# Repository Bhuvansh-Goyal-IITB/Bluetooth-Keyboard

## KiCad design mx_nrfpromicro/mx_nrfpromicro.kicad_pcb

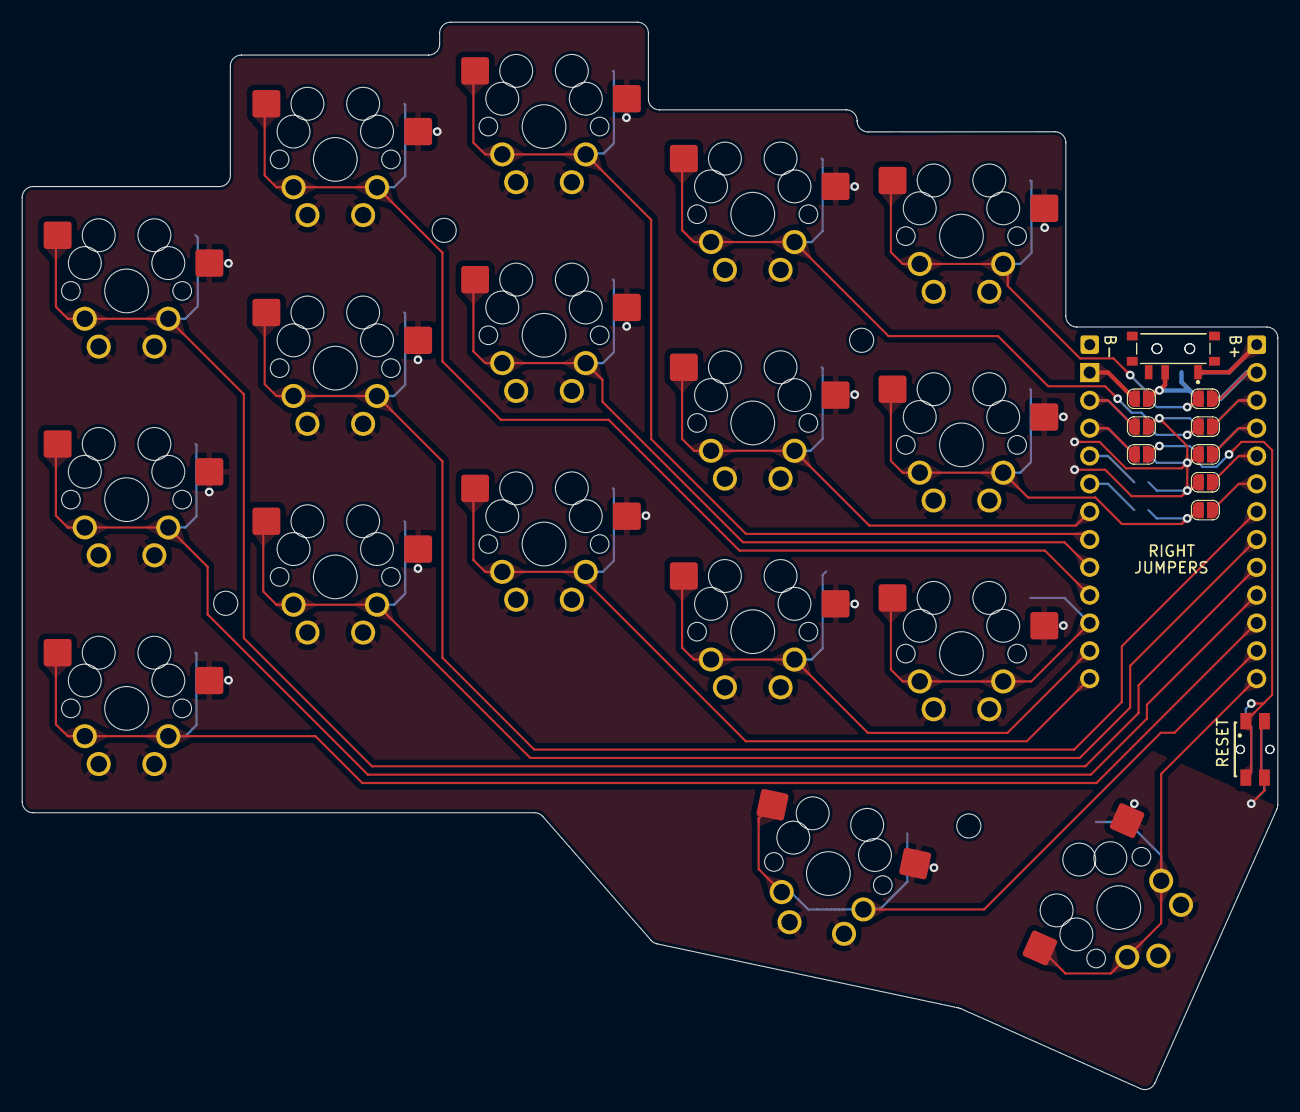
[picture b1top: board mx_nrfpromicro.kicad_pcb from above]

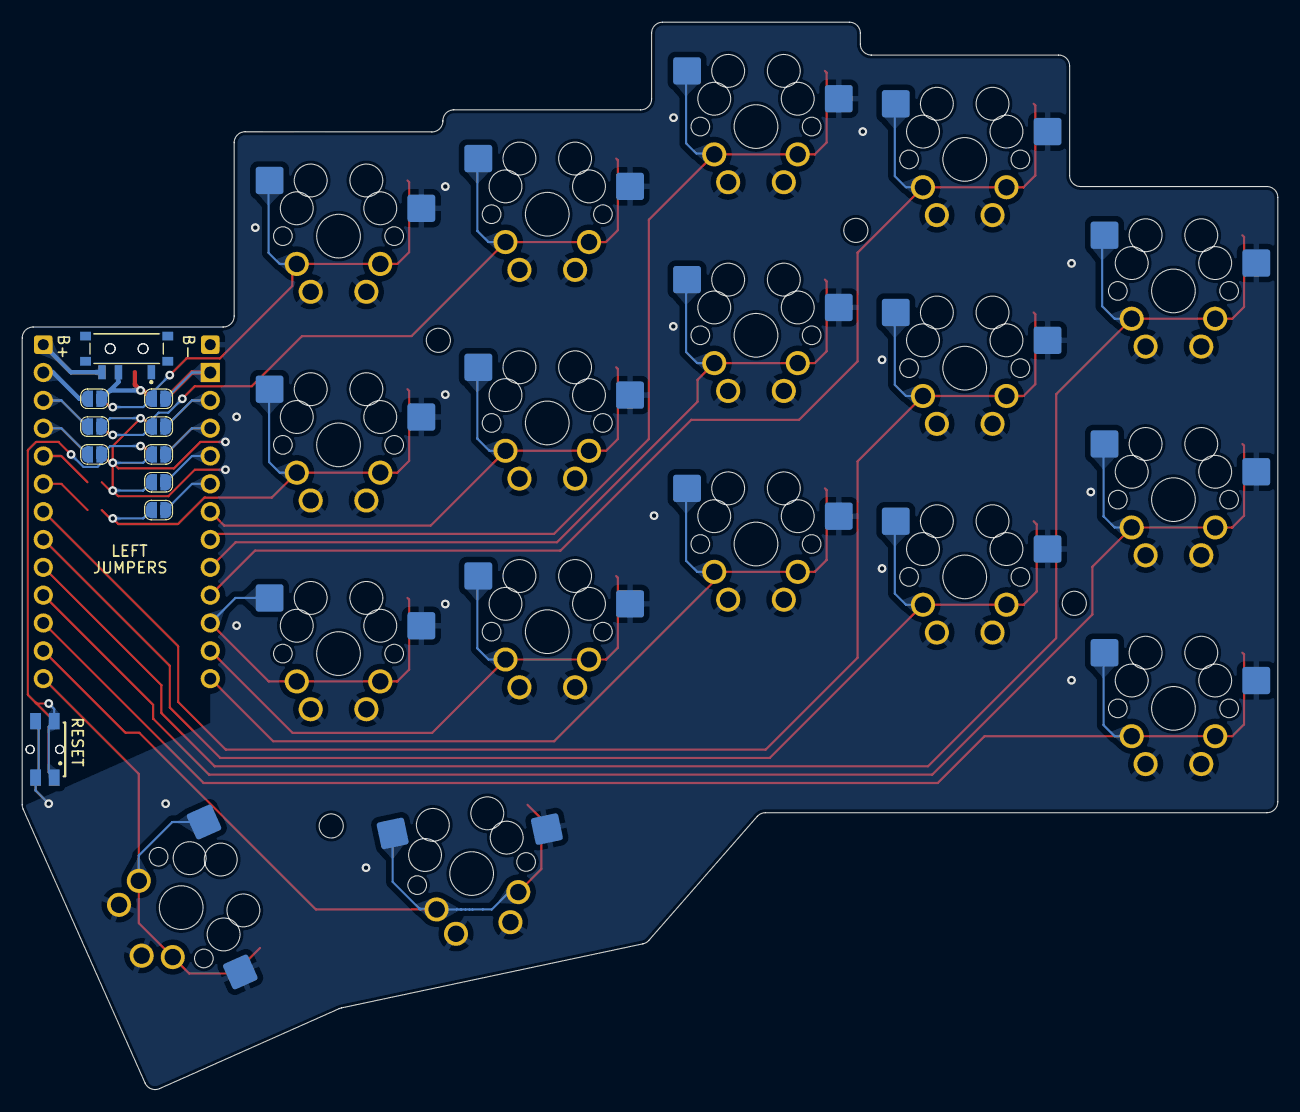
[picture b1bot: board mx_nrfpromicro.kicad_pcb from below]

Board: 2 copper layers, 114.6 x 97.4 mm, 44 parts (10 on the bottom side), 31 nets.

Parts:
H1, H2, H3, H4: MountingHole; MountingHole_2.2mm_M2
JP1, JP2, JP3, JP4, JP5, JP6, JP7, JP8, JP9, JP10, JP11, JP12, JP13, JP16, JP17, JP20: SolderJumper_2_Open; Solder_Jumper
S1, S2: 436331045822; 4363X10458XX
SW1, SW2, SW3, SW4, SW5, SW6, SW7, SW8, SW9, SW10, SW11, SW12, SW13, SW14, SW15: SW_Push_45deg; MX_Reversible_Optional_1u
SW16, SW17: SW_Push_45deg; MX_Reversible_Optional_1.5u
SW18, SW19: MLL1200S; SW_MLL1200S
TP1, TP2: TestPoint_Small; Test_Point
U1: Nice_Nano_V2

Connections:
1: JP1.2 (B), JP2.2 (B), U1.1
2: JP7.2 (B), JP8.2 (B), U1.2 (0)
3: JP9.2 (B), JP10.2 (B), U1.3 (GND)
4: JP13.2 (B), U1.4 (GND)
5: JP17.2 (B), U1.5 (2)
20: JP20.2 (B), U1.20 (21)
21: JP16.2 (B), U1.21 (3.3v)
22: JP11.2 (B), JP12.2 (B), U1.22 (RST)
23: JP5.2 (B), JP6.2 (B), U1.23 (GND)
24: JP3.2 (B), JP4.2 (B), U1.24 (B+)
B+: JP2.1 (A), JP3.1 (A), SW18.2, SW19.2
GND: JP5.1 (A), JP8.1 (A), JP9.1 (A), JP12.1 (A), JP13.1 (A), JP16.1 (A), S1.2, S1.4, S2.2, S2.4, SW1.2, SW2.2, SW3.2, SW4.2, SW5.2, SW6.2, SW7.2, SW8.2, SW9.2, SW10.2, SW11.2, SW12.2, SW13.2, SW14.2, SW15.2, SW16.2, SW17.2, TP1.1
unnamed: SW18.3, SW19.1, TP2.1
RST: JP10.1 (A), JP11.1 (A), S1.1, S1.3, S2.1, S2.3
SW1: SW1.1, U1.17 (18)
SW2: SW2.1, U1.9 (6)
SW3: SW3.1, U1.7 (4)
SW4: JP6.1 (A), JP7.1 (A), SW4.1
SW5: JP1.1 (A), JP4.1 (A), SW5.1
SW6: SW6.1, U1.16 (15)
SW7: SW7.1, U1.19 (20)
SW8: SW8.1, U1.8 (5)
SW9: SW9.1, U1.6 (3)
SW10: JP17.1 (A), JP20.1 (A), SW10.1
SW11: SW11.1, U1.15 (14)
SW12: SW12.1, U1.18 (19)
SW13: SW13.1, U1.12 (9)
SW14: SW14.1, U1.11 (8)
SW15: SW15.1, U1.10 (7)
SW16: SW16.1, U1.14 (16)
SW17: SW17.1, U1.13 (10)

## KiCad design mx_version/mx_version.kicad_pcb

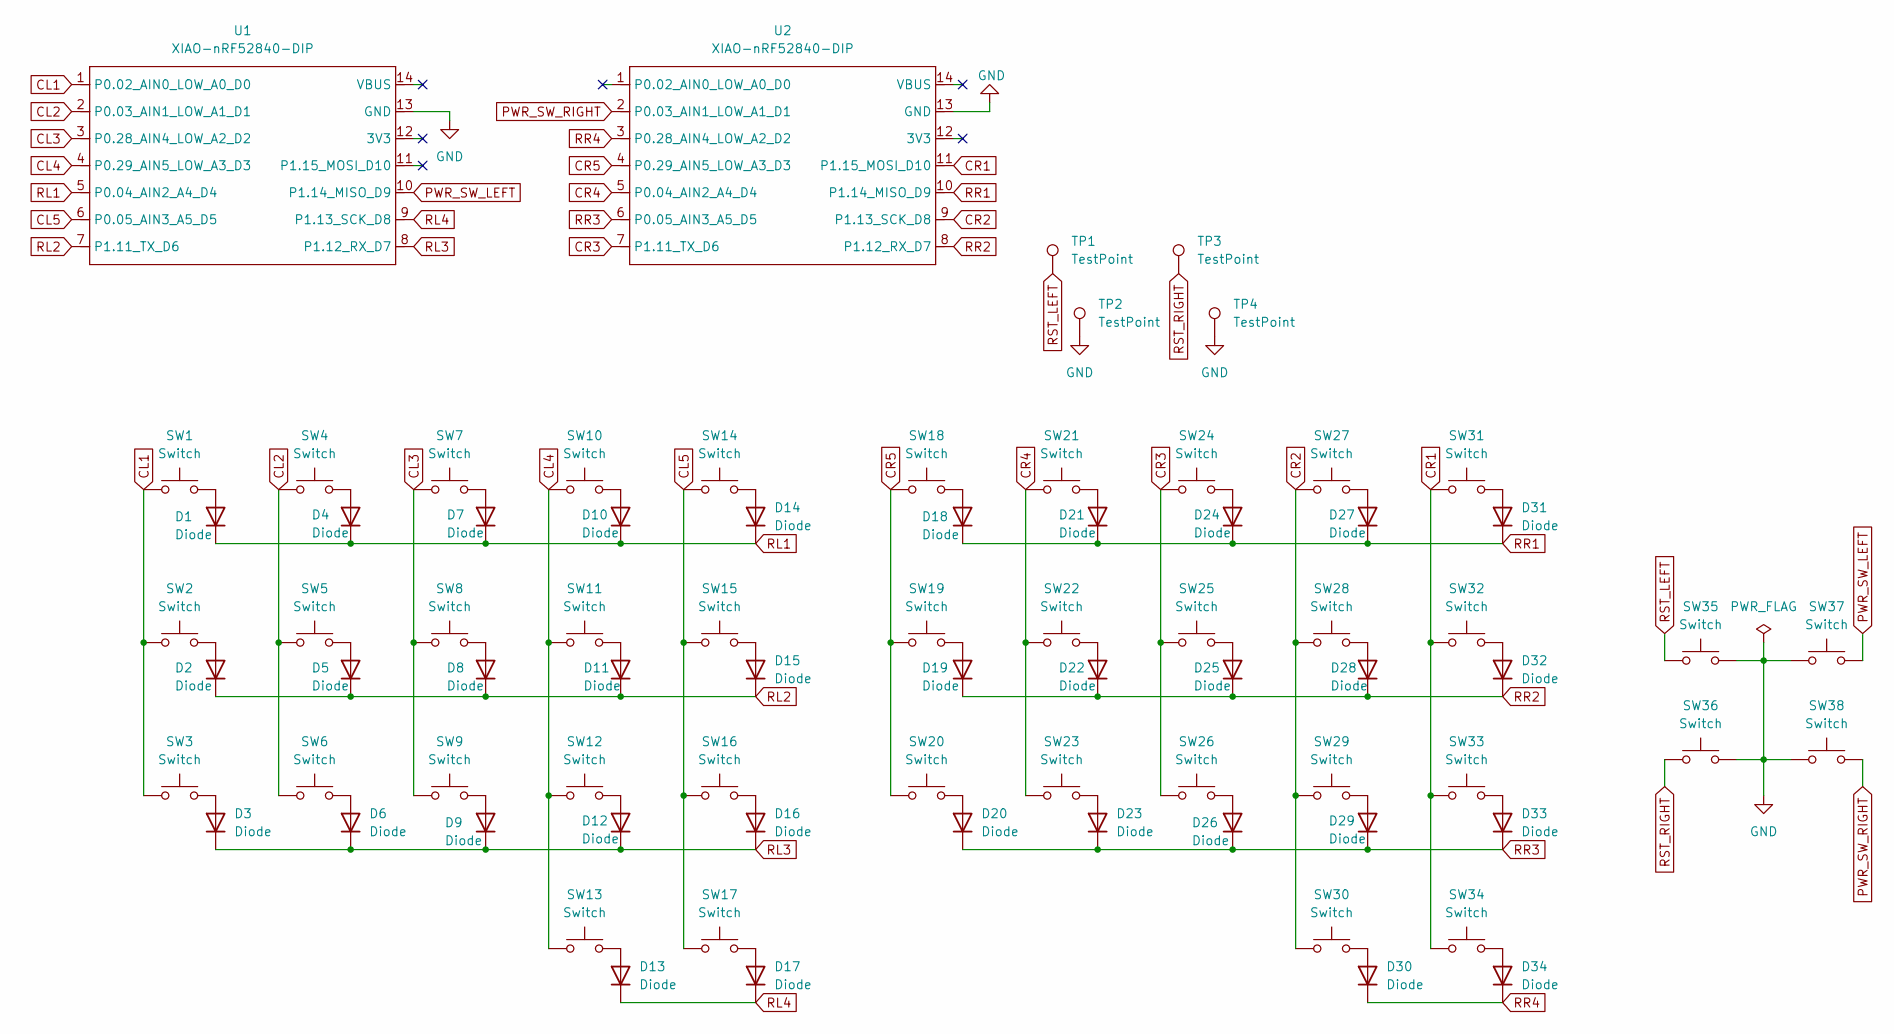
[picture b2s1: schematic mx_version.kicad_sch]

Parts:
D1, D2, D3, D4, D5, D6, D7, D8, D9, D10, D11, D12, D13, D14, D15, D16, D17, D18, D19, D20, D21, D22, D23, D24, D25, D26, D27, D28, D29, D30, D31, D32, D33, D34: Diode; Diode_SOD-123
SW1, SW2, SW3, SW4, SW5, SW6, SW7, SW8, SW9, SW10, SW11, SW12, SW14, SW15, SW16, SW18, SW19, SW20, SW21, SW22, SW23, SW24, SW25, SW26, SW27, SW28, SW29, SW31, SW32, SW33: Switch; Hotswap_MX_WSS_1.00u
SW13, SW17, SW30, SW34: Switch; Hotswap_MX_WSS_1.50u
SW35, SW36, SW37, SW38: Switch; SW_SPST_EVQP7A_ HandSoldering
TP1, TP2, TP3, TP4: TestPoint; TestPoint_Pad_D2.0mm
U1, U2: XIAO-nRF52840-DIP; XIAO-nRF52840-BG

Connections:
CL1: SW1.1, SW2.1, SW3.1, U1.1 (P0.02_AIN0_LOW_A0_D0)
CL2: SW4.1, SW5.1, SW6.1, U1.2 (P0.03_AIN1_LOW_A1_D1)
CL3: SW7.1, SW8.1, SW9.1, U1.3 (P0.28_AIN4_LOW_A2_D2)
CL4: SW10.1, SW11.1, SW12.1, SW13.1, U1.4 (P0.29_AIN5_LOW_A3_D3)
CL5: SW14.1, SW15.1, SW16.1, SW17.1, U1.6 (P0.05_AIN3_A5_D5)
CR1: SW31.1, SW32.1, SW33.1, SW34.1, U2.11 (P1.15_MOSI_D10)
CR2: SW27.1, SW28.1, SW29.1, SW30.1, U2.9 (P1.13_SCK_D8)
CR3: SW24.1, SW25.1, SW26.1, U2.7 (P1.11_TX_D6)
CR4: SW21.1, SW22.1, SW23.1, U2.5 (P0.04_AIN2_A4_D4)
CR5: SW18.1, SW19.1, SW20.1, U2.4 (P0.29_AIN5_LOW_A3_D3)
GND: SW35.2, SW36.2, SW37.1, SW38.1, TP2.1, TP4.1, U1.13 (GND), U2.13 (GND)
unnamed: D1.2 (A), SW1.2
unnamed: D2.2 (A), SW2.2
unnamed: D3.2 (A), SW3.2
unnamed: D4.2 (A), SW4.2
unnamed: D5.2 (A), SW5.2
unnamed: D6.2 (A), SW6.2
unnamed: D7.2 (A), SW7.2
unnamed: D8.2 (A), SW8.2
unnamed: D9.2 (A), SW9.2
unnamed: D10.2 (A), SW10.2
unnamed: D11.2 (A), SW11.2
unnamed: D12.2 (A), SW12.2
unnamed: D13.2 (A), SW13.2
unnamed: D14.2 (A), SW14.2
unnamed: D15.2 (A), SW15.2
unnamed: D16.2 (A), SW16.2
unnamed: D17.2 (A), SW17.2
unnamed: D18.2 (A), SW18.2
unnamed: D19.2 (A), SW19.2
unnamed: D20.2 (A), SW20.2
unnamed: D21.2 (A), SW21.2
unnamed: D22.2 (A), SW22.2
unnamed: D23.2 (A), SW23.2
unnamed: D24.2 (A), SW24.2
unnamed: D25.2 (A), SW25.2
unnamed: D26.2 (A), SW26.2
unnamed: D27.2 (A), SW27.2
unnamed: D28.2 (A), SW28.2
unnamed: D29.2 (A), SW29.2
unnamed: D30.2 (A), SW30.2
unnamed: D31.2 (A), SW31.2
unnamed: D32.2 (A), SW32.2
unnamed: D33.2 (A), SW33.2
unnamed: D34.2 (A), SW34.2
PWR_SW_LEFT: SW37.2, U1.10 (P1.14_MISO_D9)
PWR_SW_RIGHT: SW38.2, U2.2 (P0.03_AIN1_LOW_A1_D1)
RL1: D1.1 (K), D4.1 (K), D7.1 (K), D10.1 (K), D14.1 (K), U1.5 (P0.04_AIN2_A4_D4)
RL2: D2.1 (K), D5.1 (K), D8.1 (K), D11.1 (K), D15.1 (K), U1.7 (P1.11_TX_D6)
RL3: D3.1 (K), D6.1 (K), D9.1 (K), D12.1 (K), D16.1 (K), U1.8 (P1.12_RX_D7)
RL4: D13.1 (K), D17.1 (K), U1.9 (P1.13_SCK_D8)
RR1: D18.1 (K), D21.1 (K), D24.1 (K), D27.1 (K), D31.1 (K), U2.10 (P1.14_MISO_D9)
RR2: D19.1 (K), D22.1 (K), D25.1 (K), D28.1 (K), D32.1 (K), U2.8 (P1.12_RX_D7)
RR3: D20.1 (K), D23.1 (K), D26.1 (K), D29.1 (K), D33.1 (K), U2.6 (P0.05_AIN3_A5_D5)
RR4: D30.1 (K), D34.1 (K), U2.3 (P0.28_AIN4_LOW_A2_D2)
RST_LEFT: SW35.1, TP1.1
RST_RIGHT: SW36.1, TP3.1

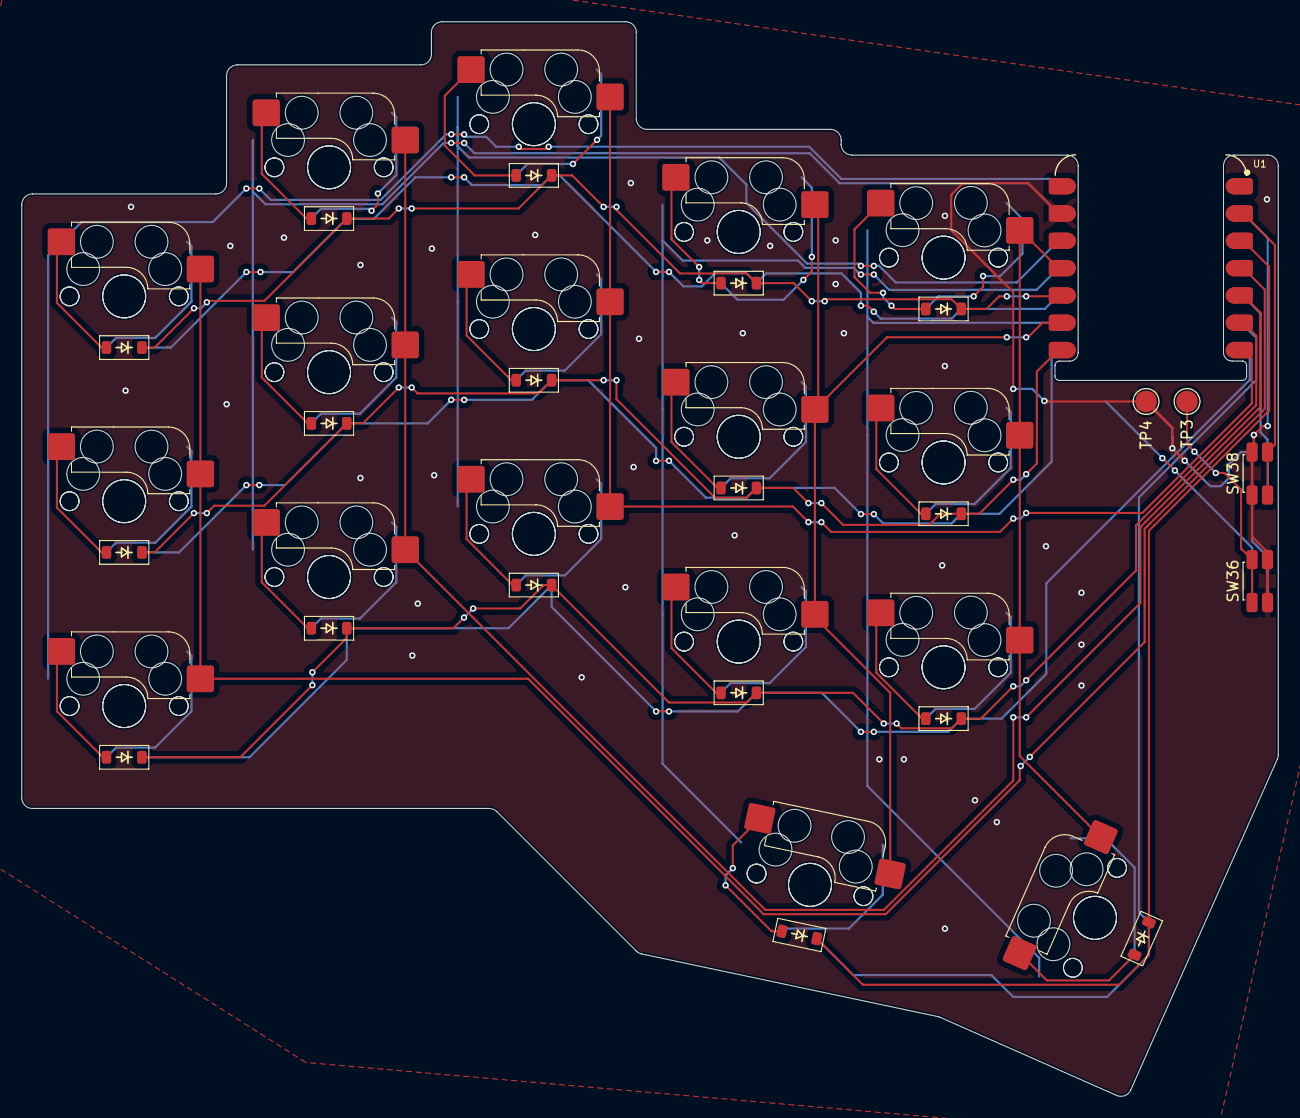
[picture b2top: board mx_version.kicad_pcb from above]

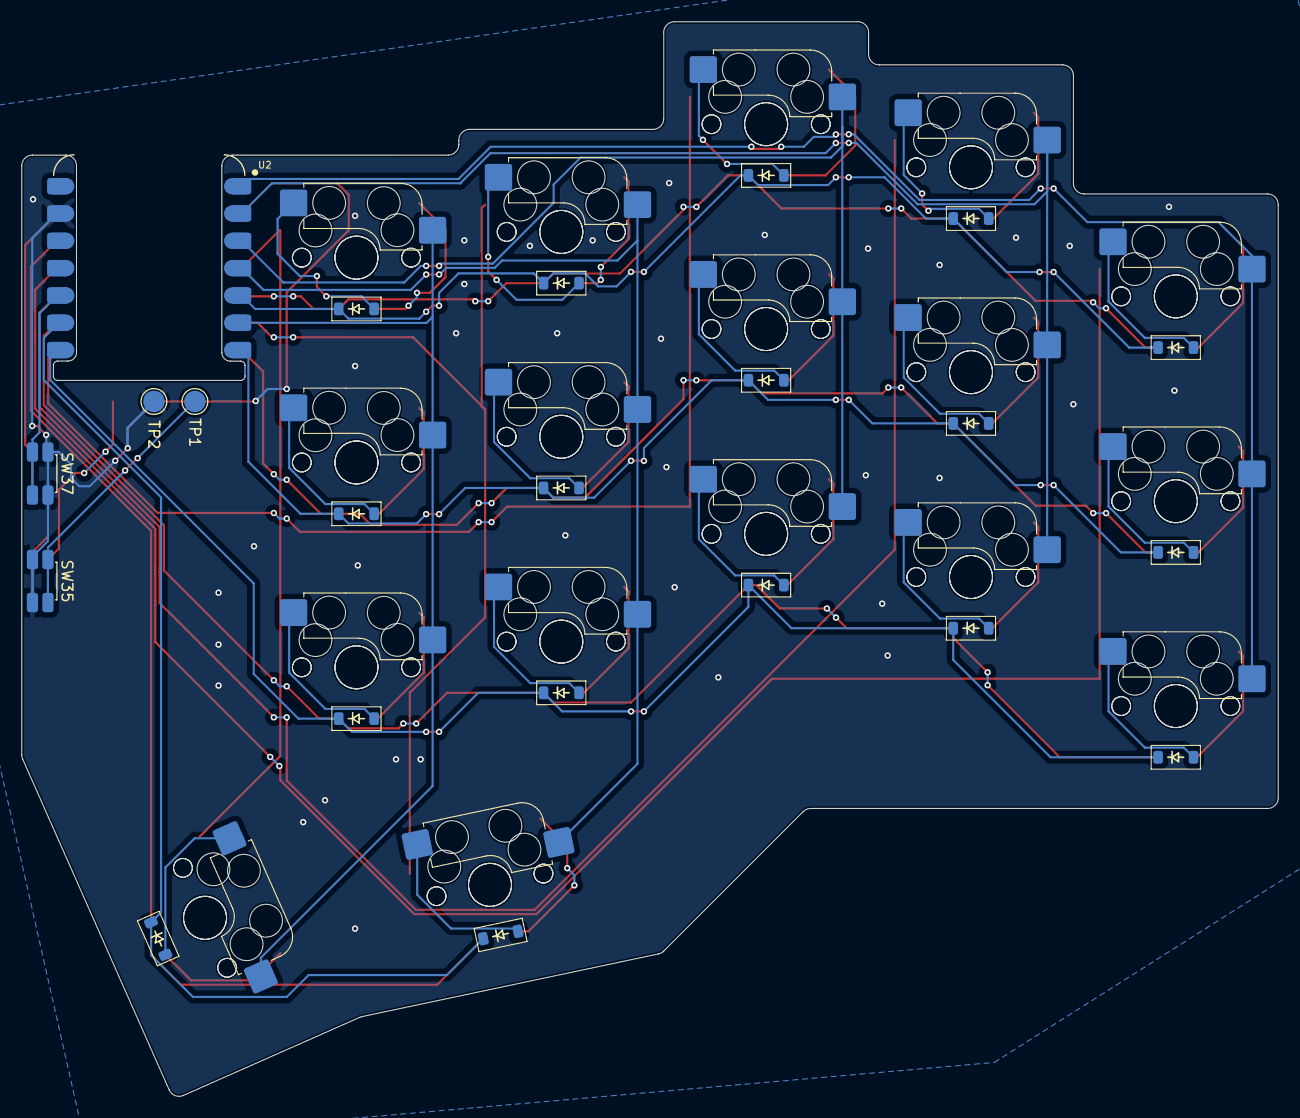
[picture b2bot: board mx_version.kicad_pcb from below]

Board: 2 copper layers, 116.9 x 99.9 mm, 78 parts (39 on the bottom side), 57 nets.

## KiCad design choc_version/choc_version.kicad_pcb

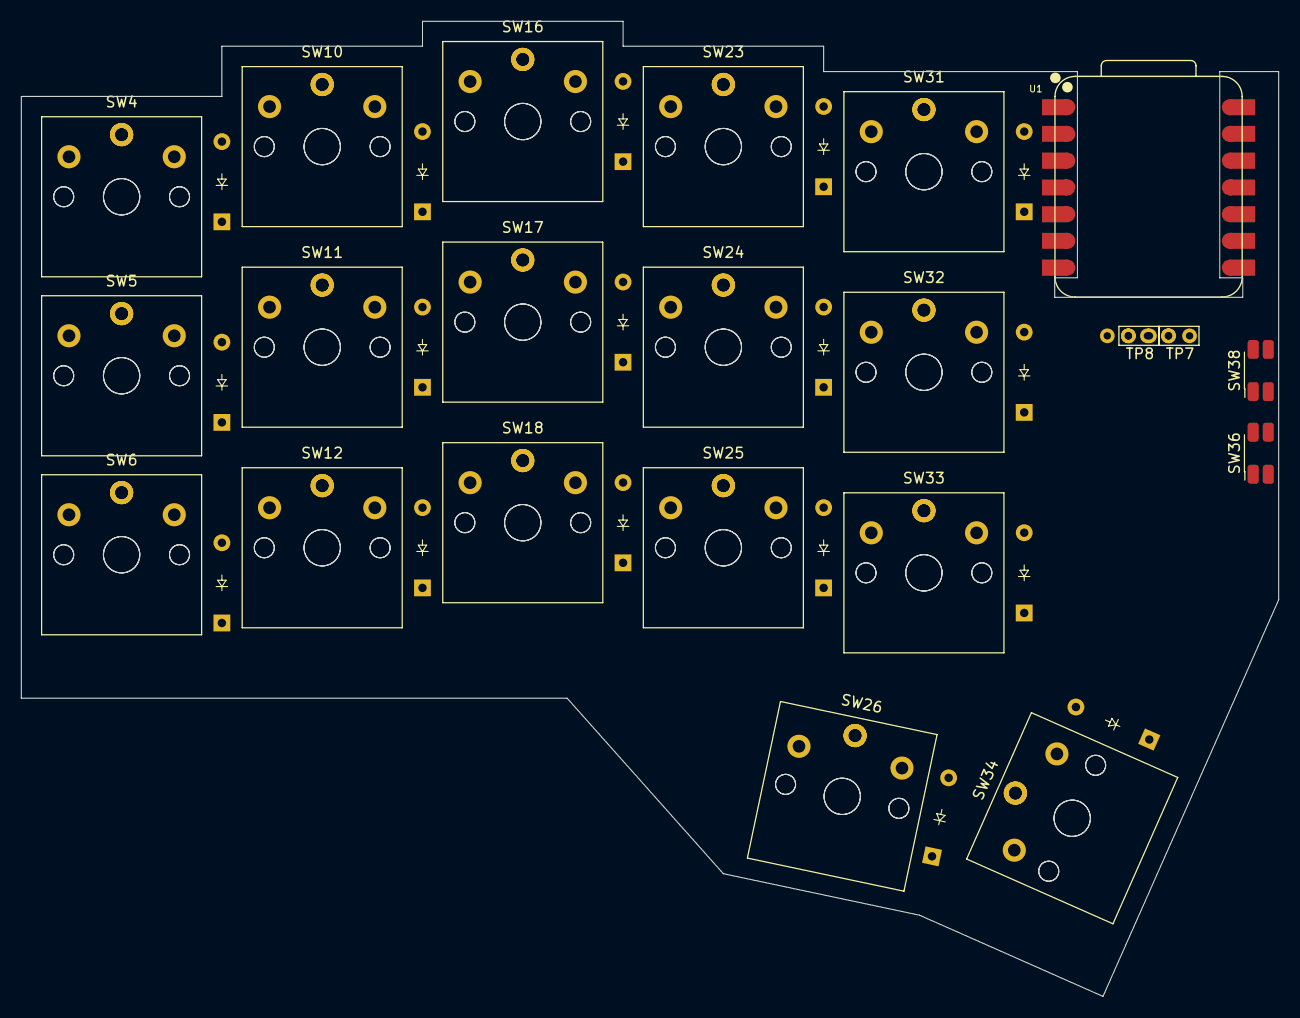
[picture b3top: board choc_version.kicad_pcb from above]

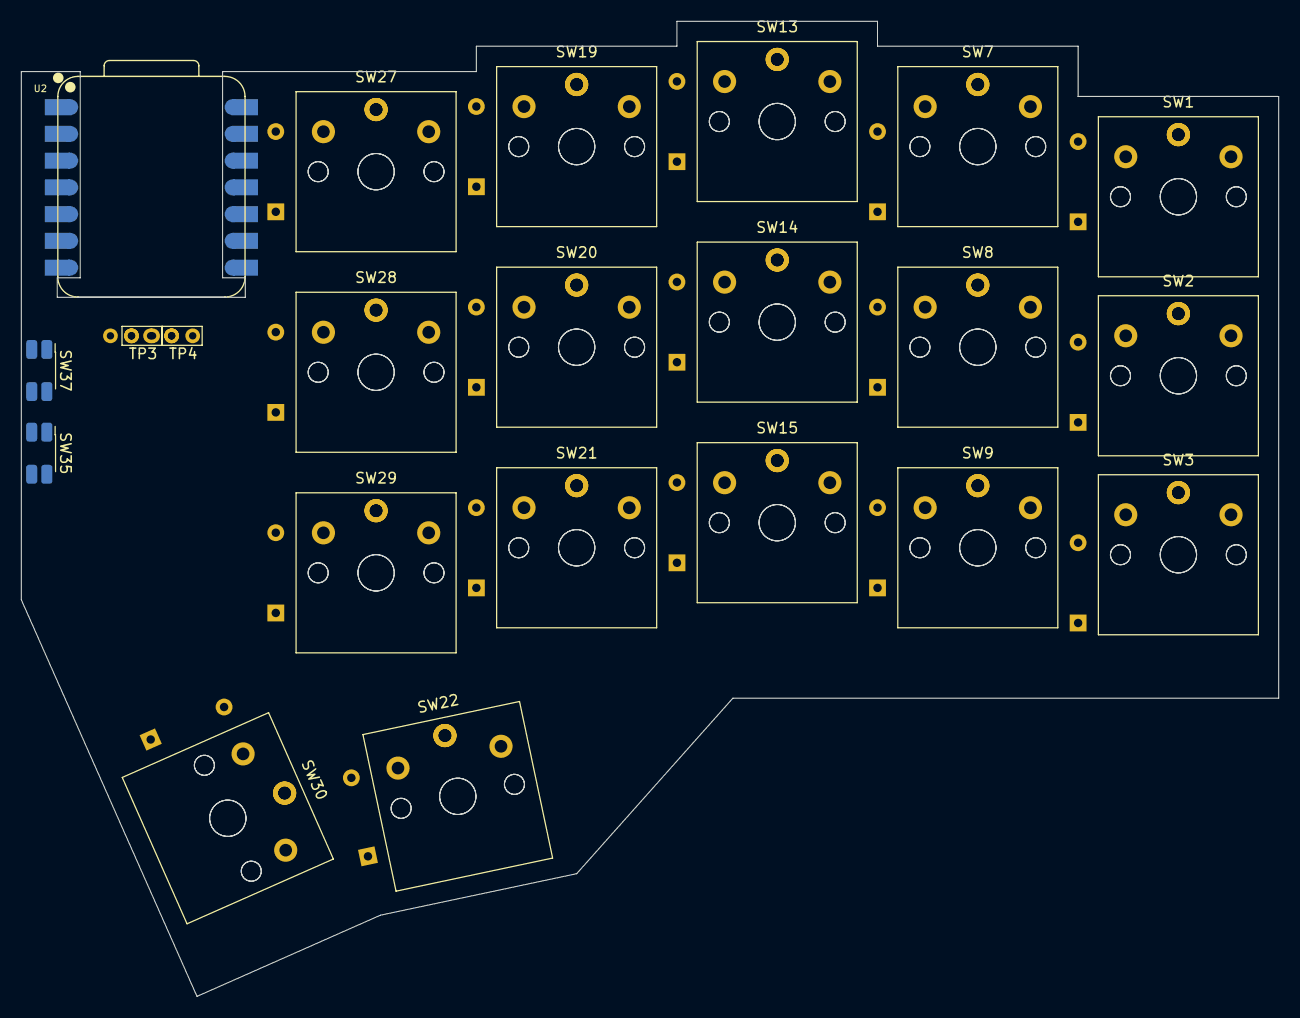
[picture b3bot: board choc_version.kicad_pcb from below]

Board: 2 copper layers, 119.4 x 92.6 mm, 61 parts (22 on the bottom side), 36 nets, no tracks yet.

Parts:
D1, D2, D3, D4, D5, D6, D7, D8, D9, D10, D11, D12, D13, D14, D15, D16, D17: Diode; Diode_DO-35
SW1, SW2, SW3, SW4, SW5, SW6, SW7, SW8, SW9, SW10, SW11, SW12, SW13, SW14, SW15, SW16, SW17, SW18, SW19, SW20, SW21, SW22, SW23, SW24, SW25, SW26, SW27, SW28, SW29, SW31, SW32, SW33: Switch; Choc_V1_1.00u
SW30, SW34: Switch; Choc_V1_1.50u
SW35, SW36, SW37, SW38: Switch; SW_SPST_EVQP7A_ HandSoldering
TP3, TP4, TP7, TP8: TestPoint; TestPoint_Bridge_Pitch2.0mm_Drill0.7mm
U1, U2: XIAO-nRF52840-DIP; XIAO-nRF52840-BG

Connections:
CL1: SW4.1, SW5.1, SW6.1, U1.1 (P0.02_AIN0_LOW_A0_D0)
CL2: SW10.1, SW11.1, SW12.1, U1.2 (P0.03_AIN1_LOW_A1_D1)
CL3: SW16.1, SW17.1, SW18.1, U1.3 (P0.28_AIN4_LOW_A2_D2)
CL4: SW23.1, SW24.1, SW25.1, SW26.1, U1.4 (P0.29_AIN5_LOW_A3_D3)
CL5: SW31.1, SW32.1, SW33.1, SW34.1, U1.5 (P0.04_AIN2_A4_D4)
CR1: SW1.1, SW2.1, SW3.1, U2.1 (P0.02_AIN0_LOW_A0_D0)
CR2: SW7.1, SW8.1, SW9.1, U2.2 (P0.03_AIN1_LOW_A1_D1)
CR3: SW13.1, SW14.1, SW15.1, U2.3 (P0.28_AIN4_LOW_A2_D2)
CR4: SW19.1, SW20.1, SW21.1, SW22.1, U2.4 (P0.29_AIN5_LOW_A3_D3)
CR5: SW27.1, SW28.1, SW29.1, SW30.1, U2.5 (P0.04_AIN2_A4_D4)
GND: SW35.2, SW36.2, SW37.1, SW38.1, TP4.1, TP8.1, U1.13 (GND), U2.13 (GND)
unnamed: D1.2 (A), SW1.2, SW4.2
unnamed: D2.2 (A), SW2.2, SW5.2
unnamed: D3.2 (A), SW3.2, SW6.2
unnamed: D4.2 (A), SW7.2, SW10.2
unnamed: D5.2 (A), SW8.2, SW11.2
unnamed: D6.2 (A), SW9.2, SW12.2
unnamed: D7.2 (A), SW13.2, SW16.2
unnamed: D8.2 (A), SW14.2, SW17.2
unnamed: D9.2 (A), SW15.2, SW18.2
unnamed: D10.2 (A), SW19.2, SW23.2
unnamed: D11.2 (A), SW20.2, SW24.2
unnamed: D12.2 (A), SW21.2, SW25.2
unnamed: D13.2 (A), SW22.2, SW26.2
unnamed: D14.2 (A), SW27.2, SW31.2
unnamed: D15.2 (A), SW28.2, SW32.2
unnamed: D16.2 (A), SW29.2, SW33.2
unnamed: D17.2 (A), SW30.2, SW34.2
PWR_SWITCH_LEFT: SW37.2, U1.10 (P1.14_MISO_D9)
PWR_SWITCH_RIGHT: SW38.2, U2.10 (P1.14_MISO_D9)
R1: D1.1 (K), D4.1 (K), D7.1 (K), D10.1 (K), D14.1 (K), U1.6 (P0.05_AIN3_A5_D5), U2.6 (P0.05_AIN3_A5_D5)
R2: D2.1 (K), D5.1 (K), D8.1 (K), D11.1 (K), D15.1 (K), U1.7 (P1.11_TX_D6), U2.7 (P1.11_TX_D6)
R3: D3.1 (K), D6.1 (K), D9.1 (K), D12.1 (K), D16.1 (K), U1.8 (P1.12_RX_D7), U2.8 (P1.12_RX_D7), U2.9 (P1.13_SCK_D8)
R4: D13.1 (K), D17.1 (K), U1.9 (P1.13_SCK_D8)
RESET_LEFT: SW35.1, TP3.1
RESET_RIGHT: SW36.1, TP7.1

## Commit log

2025-02-26 initial
2025-02-26 updated library
2025-03-08 v1 final
